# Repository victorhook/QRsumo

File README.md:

# QRsumo

QRsumo is a really cool sumorobot :)

Look out for more!

## Installation instructions
```
git clone https://github.com/victorhook/QRsumo.git
git submodule init && cd kicad-libraries && git submodule update --recursive
```

## Schematic

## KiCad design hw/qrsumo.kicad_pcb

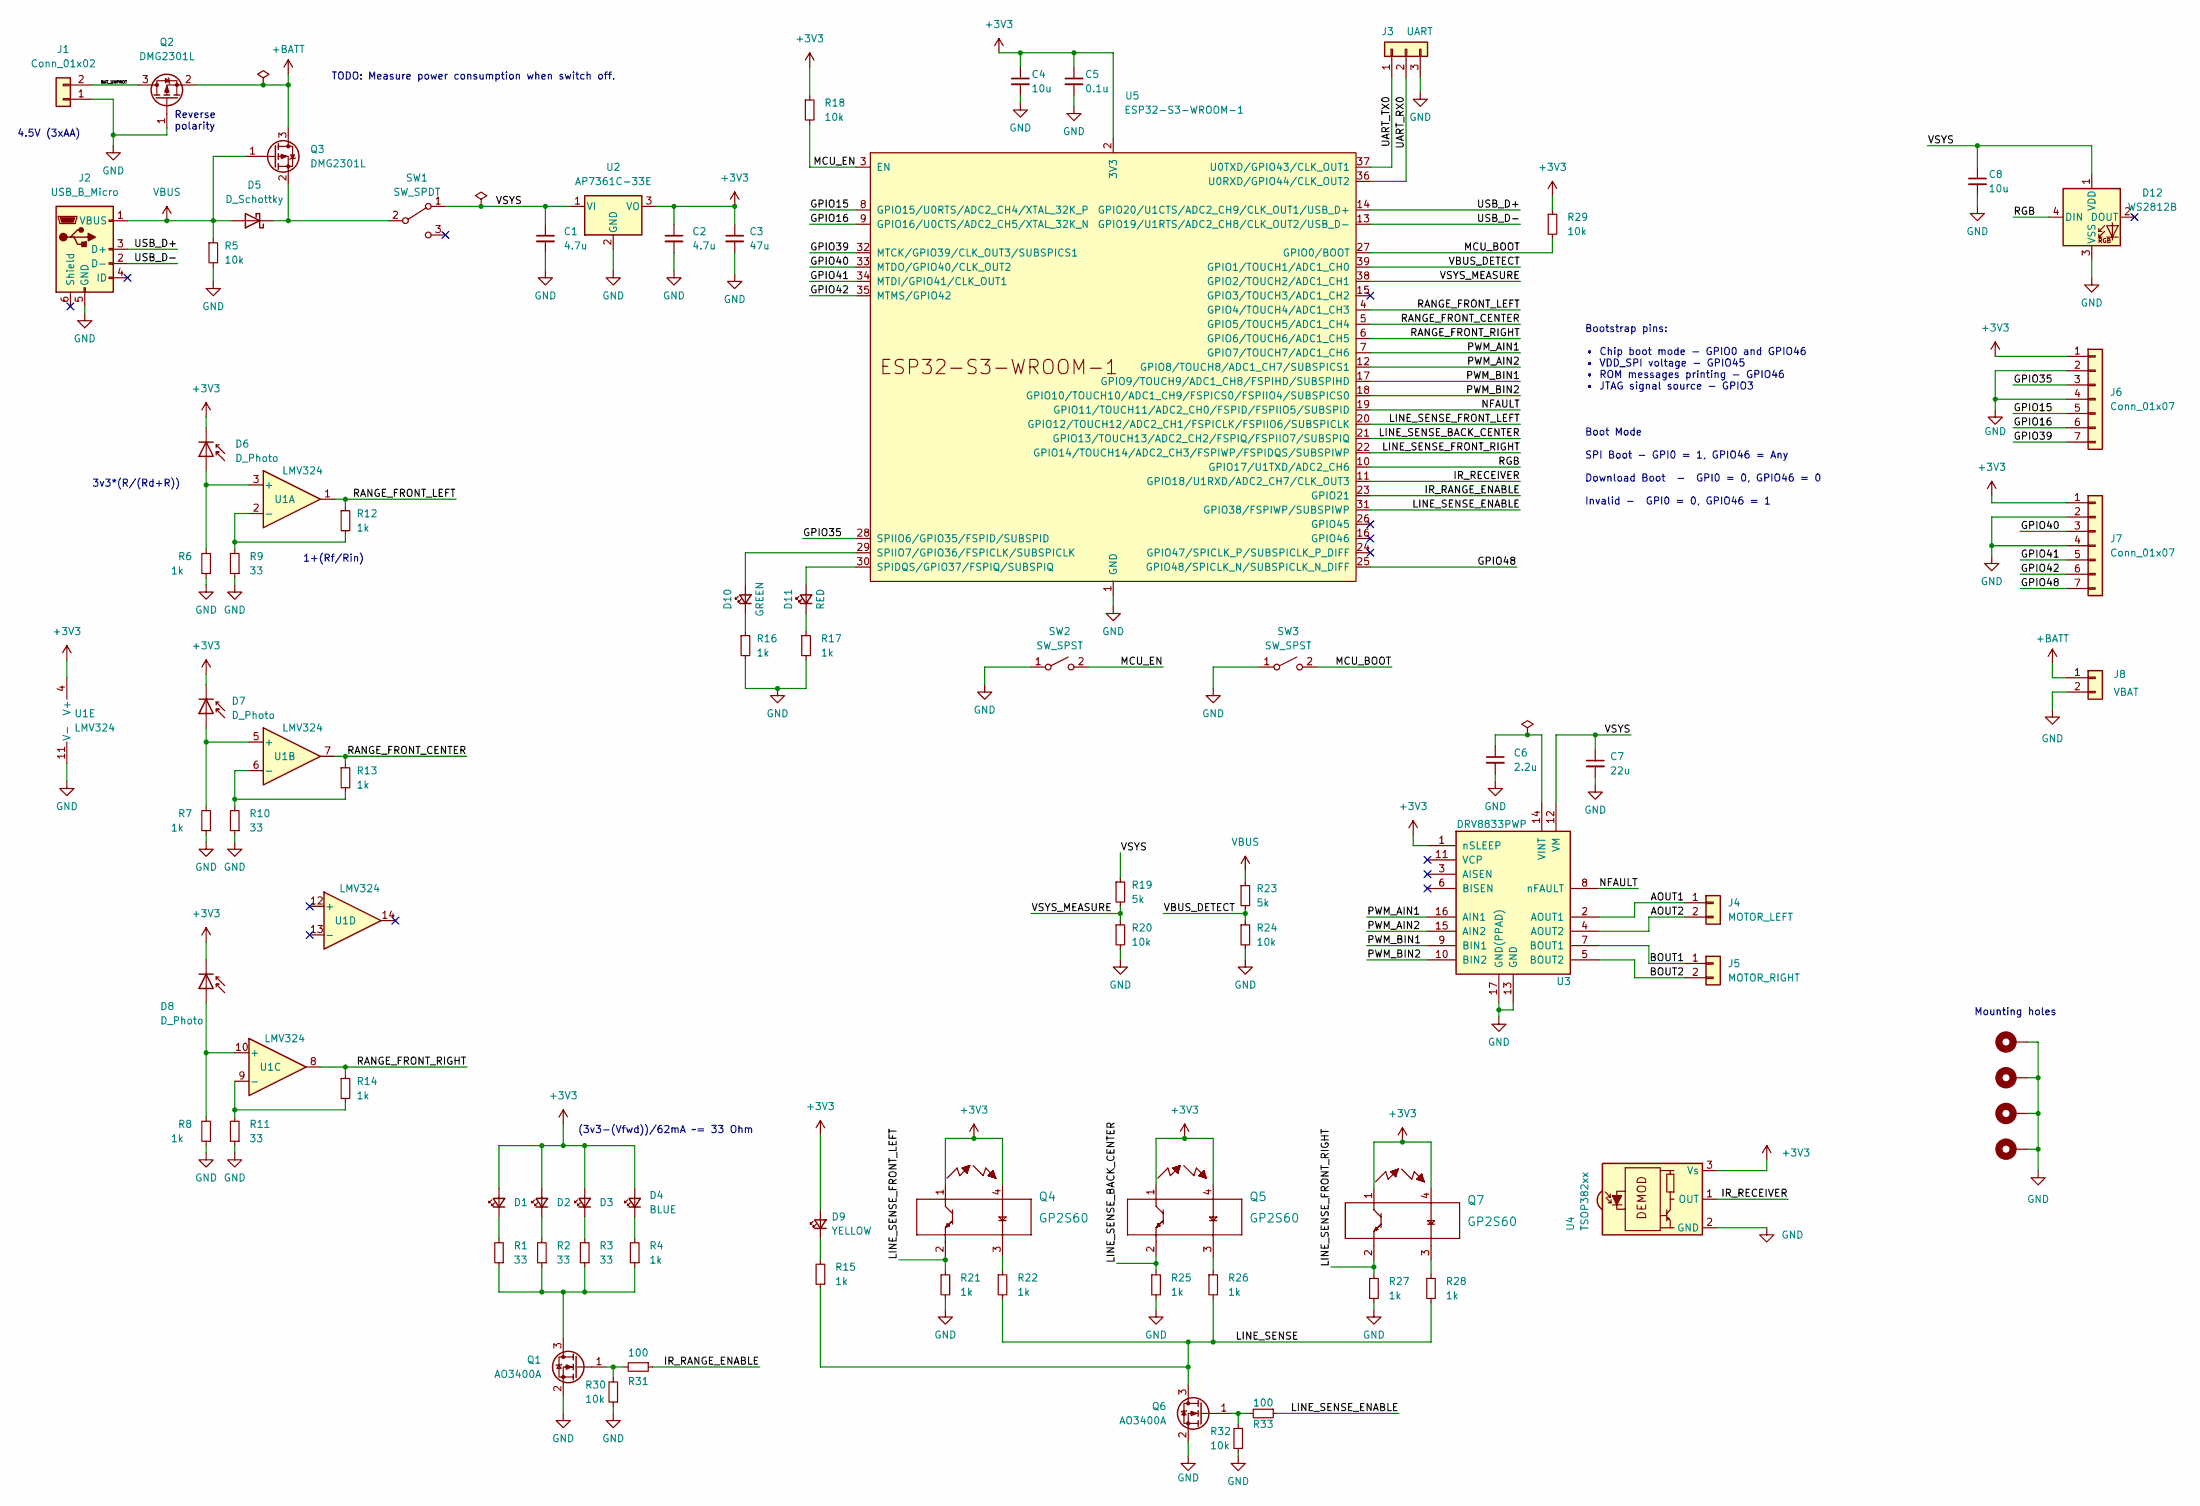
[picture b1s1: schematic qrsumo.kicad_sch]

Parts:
C1, C2: 4.7u; C_0603_1608Metric
C3: 47u; C_0603_1608Metric
C4, C8: 10u; C_0603_1608Metric
C5: 0.1u; C_0603_1608Metric
C6: 2.2u; C_0603_1608Metric
C7: 22u; C_0603_1608Metric
D1, D2, D3: LED_Small; PinHeader_1x02_P2.54mm_Vertical
D4: BLUE; LED_0603_1608Metric
D5: D_Schottky; D_SOD-123F
D6, D7, D8: D_Photo; PinHeader_1x02_P2.54mm_Vertical
D9: YELLOW; LED_0603_1608Metric
D10: GREEN; LED_0603_1608Metric
D11: RED; LED_0603_1608Metric
D12: WS2812B; LED_WS2812B_PLCC4_5.0x5.0mm_P3.2mm
H1, H2, H3, H4: MountingHole_Pad; MountingHole_2.7mm_M2.5_Pad_Via
J1: Conn_01x02; PinHeader_1x02_P2.54mm_Vertical
J2: USB_B_Micro; CONN_10118193-0001LF_AMP
J3: UART; PinHeader_1x03_P2.54mm_Vertical
J4: MOTOR_LEFT; PinHeader_1x02_P2.54mm_Vertical
J5: MOTOR_RIGHT; PinHeader_1x02_P2.54mm_Vertical
J6, J7: Conn_01x07; PinHeader_1x07_P2.54mm_Vertical
J8: VBAT; PinHeader_1x02_P2.54mm_Vertical
Q1, Q6: AO3400A; SOT-23
Q2, Q3: DMG2301L; SOT-23
Q4, Q5, Q7: GP2S60; SHARP_GP2S60
R1, R2, R3, R9, R10, R11: 33; R_0603_1608Metric
R4, R6, R7, R8, R12, R13, R14, R15, R16, R17, R21, R22, R25, R26, R27, R28: 1k; R_0603_1608Metric
R5, R18, R20, R24, R29, R30, R32: 10k; R_0603_1608Metric
R19, R23: 5k; R_0603_1608Metric
R31, R33: 100; R_0603_1608Metric
SW1: SW_SPDT; EG1206A_EWI
SW2, SW3: SW_SPST; PTS647_SPST_SNXX_SMTR2_4.5x4.5mm
U1: LMV324; TSSOP-14_4.4x5mm_P0.65mm
U2: AP7361C-33E; SOT-223-3_TabPin2; MPN AP7361C-33ER-13DITR-ND
U3: DRV8833PWP; HTSSOP-16-1EP_4.4x5mm_P0.65mm_EP3.4x5mm_Mask2.46x2.31mm_The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
U4: TSOP382xx; Vishay_MINICAST-3Pin
U5: ESP32-S3-WROOM-1; ESP32-S3-WROOM-1U

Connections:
+3V3: C2.1, C3.1, C4.1, C5.1, D1.2 (A), D2.2 (A), D3.2 (A), D4.2 (A), D6.1 (K), D7.1 (K), D8.1 (K), D9.2 (A), J6.1, J7.1, Q4.1, Q4.4, Q5.1, Q5.4, Q7.1, Q7.4, R18.1, R29.1, U1.4 (V+), U2.3 (VO), U3.1 (nSLEEP), U4.3 (Vs), U5.2 (3V3)
+BATT: J8.1, Q2.2 (S), Q3.3 (D)
/AOUT1: J4.1, U3.2 (AOUT1)
/AOUT2: J4.2, U3.4 (AOUT2)
/BAT_UNPROT: J1.2, Q2.3 (D)
/BOUT1: J5.1, U3.7 (BOUT1)
/BOUT2: J5.2, U3.5 (BOUT2)
/GPIO15: J6.5, U5.8 (GPIO15/U0RTS/ADC2_CH4/XTAL_32K_P)
/GPIO16: J6.6, U5.9 (GPIO16/U0CTS/ADC2_CH5/XTAL_32K_N)
/GPIO35: J6.3, U5.28 (SPIIO6/GPIO35/FSPID/SUBSPID)
/GPIO39: J6.7, U5.32 (MTCK/GPIO39/CLK_OUT3/SUBSPICS1)
/GPIO40: J7.3, U5.33 (MTDO/GPIO40/CLK_OUT2)
/GPIO41: J7.5, U5.34 (MTDI/GPIO41/CLK_OUT1)
/GPIO42: J7.6, U5.35 (MTMS/GPIO42)
/GPIO48: J7.7, U5.25 (GPIO48/SPICLK_N/SUBSPICLK_N_DIFF)
/IR_RANGE_ENABLE: R31.1, U5.23 (GPIO21)
/IR_RECEIVER: U4.1 (OUT), U5.11 (GPIO18/U1RXD/ADC2_CH7/CLK_OUT3)
/LINE_SENSE: Q6.3 (D), R15.1, R22.2, R26.2, R28.2
/LINE_SENSE_BACK_CENTER: Q5.2, R25.1, U5.21 (GPIO13/TOUCH13/ADC2_CH2/FSPIQ/FSPIIO7/S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)
/LINE_SENSE_ENABLE: R33.1, U5.31 (GPIO38/FSPIWP/SUBSPIWP)
/LINE_SENSE_FRONT_LEFT: Q4.2, R21.1, U5.20 (GPIO12/TOUCH12/ADC2_CH1/FSPICLK/FSPIIO6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)
/LINE_SENSE_FRONT_RIGHT: Q7.2, R27.1, U5.22 (GPIO14/TOUCH14/ADC2_CH3/FSPIWP/FSPIDQS/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)
/MCU_BOOT: R29.2, SW3.2 (B), U5.27 (GPIO0/BOOT)
/MCU_EN: R18.2, SW2.2 (B), U5.3 (EN)
/NFAULT: U3.8 (nFAULT), U5.19 (GPIO11/TOUCH11/ADC2_CH0/FSPID/FSPIIO5/S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)
/PWM_AIN1: U3.16 (AIN1), U5.7 (GPIO7/TOUCH7/ADC1_CH6)
/PWM_AIN2: U3.15 (AIN2), U5.12 (GPIO8/TOUCH8/ADC1_CH7/SUBSPICS1)
/PWM_BIN1: U3.9 (BIN1), U5.17 (GPIO9/TOUCH9/ADC1_CH8/FSPIHD/SUBSPIHD)
/PWM_BIN2: U3.10 (BIN2), U5.18 (GPIO10/TOUCH10/ADC1_CH9/FSPICS0/FSPIIO4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)
/RANGE_FRONT_CENTER: R13.1, U1.7, U5.5 (GPIO5/TOUCH5/ADC1_CH4)
/RANGE_FRONT_LEFT: R12.1, U1.1, U5.4 (GPIO4/TOUCH4/ADC1_CH3)
/RANGE_FRONT_RIGHT: R14.1, U1.8, U5.6 (GPIO6/TOUCH6/ADC1_CH5)
/RGB: D12.4 (DIN), U5.10 (GPIO17/U1TXD/ADC2_CH6)
/UART_RX0: J3.2, U5.36 (U0RXD/GPIO44/CLK_OUT2)
/UART_TX0: J3.1, U5.37 (U0TXD/GPIO43/CLK_OUT1)
/USB_D+: J2.3 (D+), U5.14 (GPIO20/U1CTS/ADC2_CH9/CLK_OUT1/USB_D+)
/USB_D-: J2.2 (D-), U5.13 (GPIO19/U1RTS/ADC2_CH8/CLK_OUT2/USB_D-)
/VBUS_DETECT: R23.2, R24.1, U5.39 (GPIO1/TOUCH1/ADC1_CH0)
/VSYS: C1.1, C7.1, C8.1, D12.1 (VDD), R19.1, SW1.1 (A), U2.1 (VI), U3.12 (VM)
/VSYS_MEASURE: R19.2, R20.1, U5.38 (GPIO2/TOUCH2/ADC1_CH1)
GND: C1.2, C2.2, C3.2, C4.2, C5.2, C6.2, C7.2, C8.2, D12.3 (VSS), H1.1, H2.1, H3.1, H4.1, J1.1, J2.5 (GND), J3.3, J6.2, J6.4, J7.2, J7.4, J8.2, Q1.2 (S), Q2.1 (G), Q6.2 (S), R5.2, R6.1, R7.1, R8.1, R9.1, R10.1, R11.1, R16.2, R17.2, R20.2, R21.2, R24.2, R25.2, R27.2, R30.1, R32.1, SW2.1 (A), SW3.1 (A), U1.11 (V-), U2.2 (GND), U3.13 (GND), U3.17 (GND(PPAD)), U4.2 (GND), U5.1 (GND), U5.40 (GND), U5.41 (GND)
unnamed: C6.1, U3.14 (VINT)
unnamed: D1.1 (K), R1.2
unnamed: D2.1 (K), R2.2
unnamed: D3.1 (K), R3.2
unnamed: D4.1 (K), R4.2
unnamed: D5.1 (K), Q3.2 (S), SW1.2 (B)
unnamed: D6.2 (A), R6.2, U1.3 (+)
unnamed: D7.2 (A), R7.2, U1.5 (+)
unnamed: D8.2 (A), R8.2, U1.10 (+)
unnamed: D9.1 (K), R15.2
unnamed: D10.1 (K), R16.1
unnamed: D10.2 (A), U5.29 (SPIIO7/GPIO36/FSPICLK/SUBSPICLK)
unnamed: D11.1 (K), R17.1
unnamed: D11.2 (A), U5.30 (SPIDQS/GPIO37/FSPIQ/SUBSPIQ)
unnamed: Q1.1 (G), R30.2, R31.2
unnamed: Q1.3 (D), R1.1, R2.1, R3.1, R4.1
unnamed: Q4.3, R22.1
unnamed: Q5.3, R26.1
unnamed: Q6.1 (G), R32.2, R33.2
unnamed: Q7.3, R28.1
unnamed: R10.2, R13.2, U1.6 (-)
unnamed: R11.2, R14.2, U1.9 (-)
unnamed: R9.2, R12.2, U1.2 (-)
VBUS: D5.2 (A), J2.1 (VBUS), Q3.1 (G), R5.1, R23.1

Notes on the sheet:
3v3*(R/(Rd+R))
Mounting holes
Bootstrap pins: • Chip boot mode - GPIO0 and GPIO46 • VDD_SPI voltage - GPIO45 • ROM messages printing - GPIO46 • JTAG signal source - GPIO3 Boot Mode SPI Boot - GPI0 = 1, GPIO46 = Any Download Boot - GPI0 = 0, GPIO46 = 0 Invalid - GPI0 = 0, GPIO46 = 1
Reverse polarity
TODO: Measure power consumption when switch off.
1+(Rf/Rin)
4.5V (3xAA)
(3v3-(Vfwd))/62mA ~= 33 Ohm

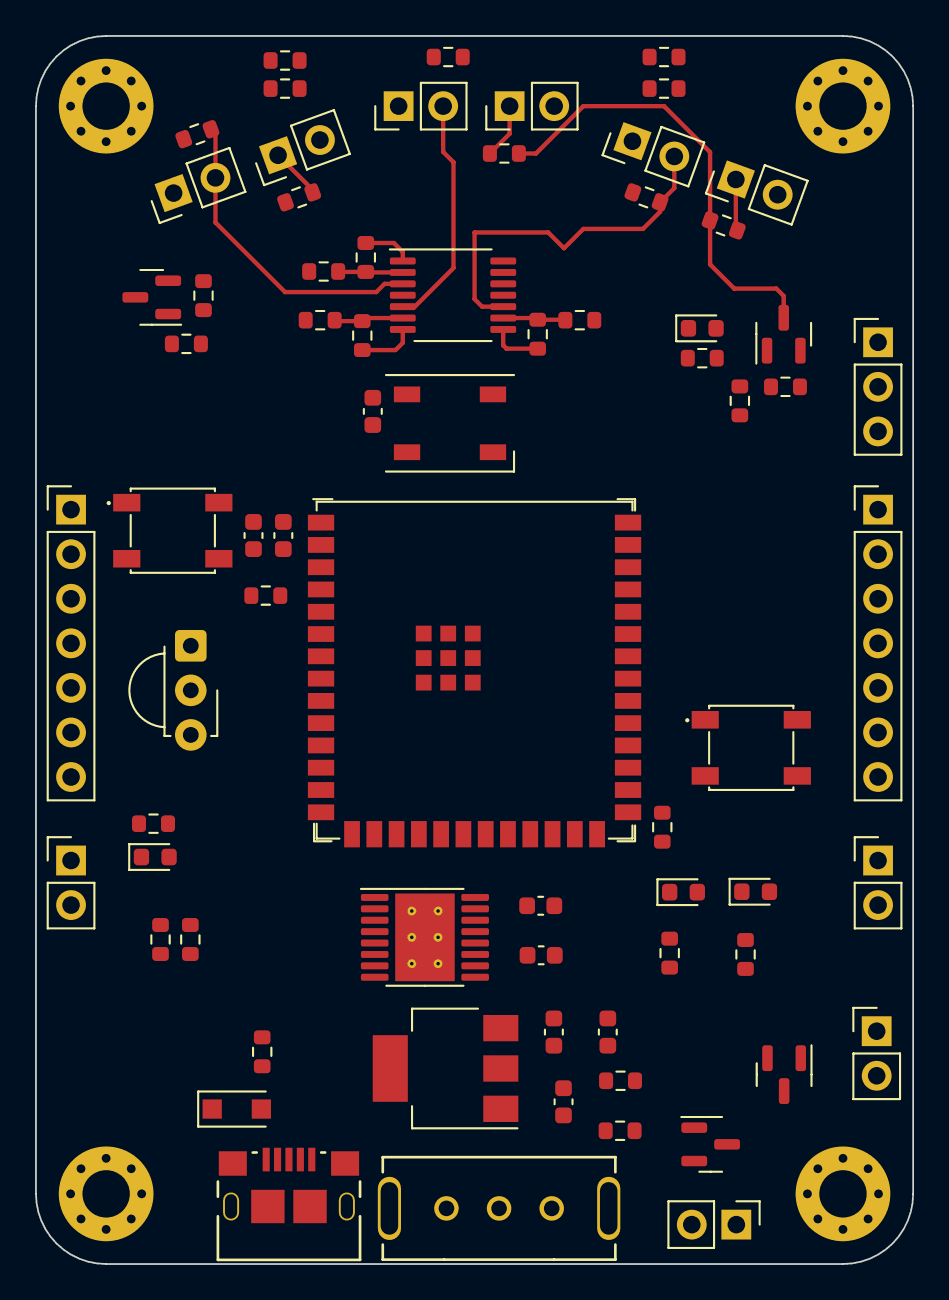
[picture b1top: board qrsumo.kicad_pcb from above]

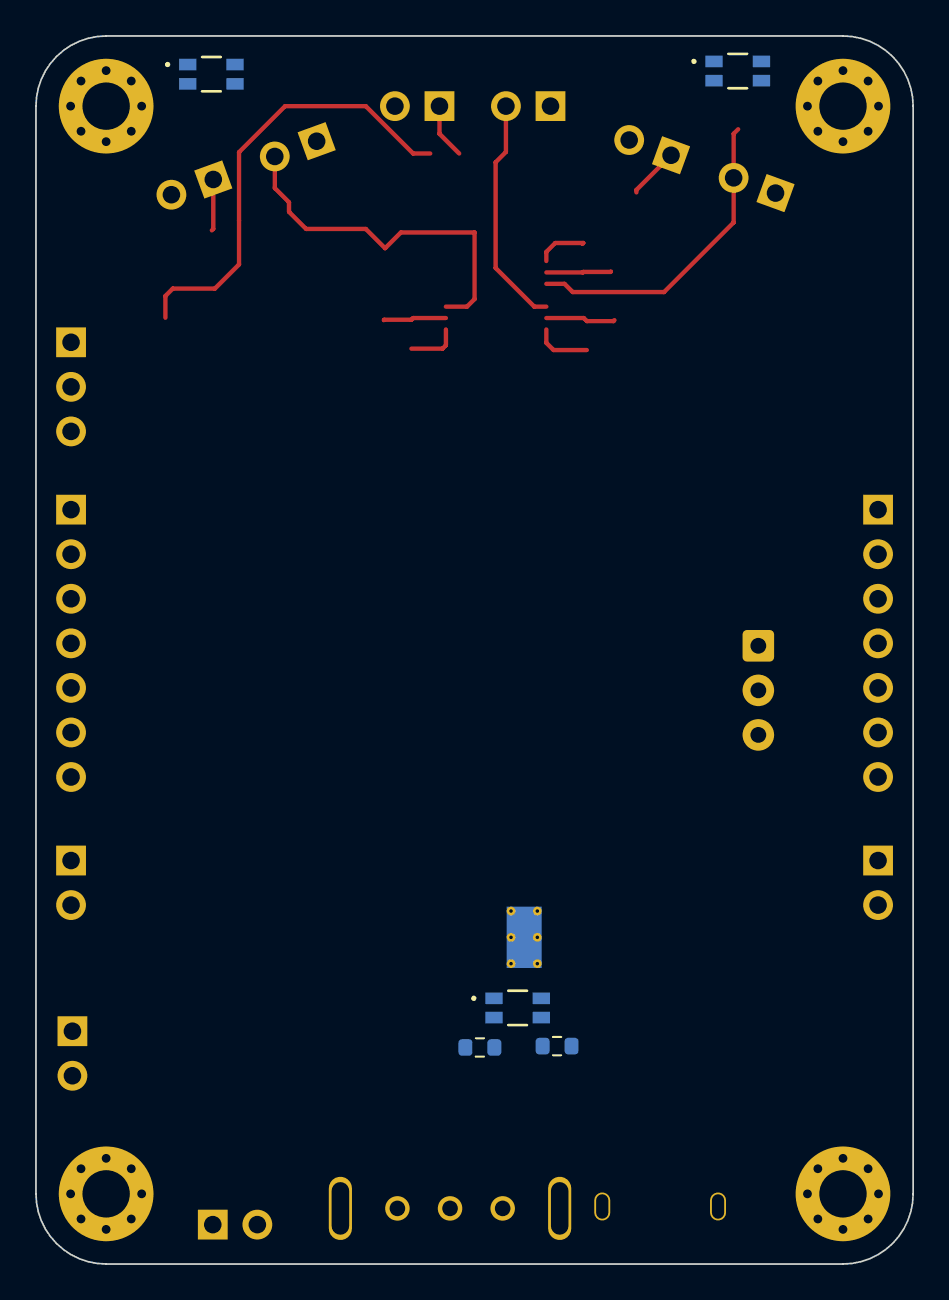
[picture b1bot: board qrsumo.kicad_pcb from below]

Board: 4 copper layers, 50.0 x 70.0 mm, 80 parts (5 on the bottom side), 65 nets.

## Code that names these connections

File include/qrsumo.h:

#ifndef QRSUMO_H
#define QRSUMO_H

#include <Arduino.h>
#include <Adafruit_NeoPixel.h>

#define PIN_VBUS_DETECT 0
#define PIN_VSYS_MEASURE 0
#define PIN_RANGE_FRONT_LEFT 0
#define PIN_RANGE_FRONT_CENTER 0
#define PIN_RANGE_FRONT_RIGHT 0
#define PIN_PWM_AIN1 0
#define PIN_PWM_AIN2 0
#define PIN_PWM_BIN1 0
#define PIN_PWM_BIN2 0
#define PIN_NFAULT 0
#define PIN_LINE_SENSE_ENABLE 0
#define PIN_LINE_SENSE_FRONT_LEFT 0
#define PIN_LINE_SENSE_BACK_CENTER 0
#define PIN_LINE_SENSE_FRONT_RIGHT 0
#define PIN_RGB 0
#define PIN_LED_GREEN 0
#define PIN_LED_RED 0
#define PIN_IR_RECEIVER 0
#define PIN_IR_RANGE_ENABLE 0


typedef enum
{
    MOTOR_LEFT  = 0,
    MOTOR_RIGHT = 1
} motor_type_t;

typedef enum
{
    DIRECTION_FORWARD  = 0,
    DIRECTION_BACKWARD = 1
} direction_t;

struct Motor {
    motor_type_t type;
    direction_t  direction;
    uint8_t      duty;
    uint8_t      pin_in1;
    uint8_t      pin_in2;
};


class QRsumo
{
    public:
        QRsumo();
        ~QRsumo();
        void init();

        /*
        Parameters:
            color: 24 bit RGB, MSB.
        */
        void ledSetRgb(const uint32_t color);
        void ledSetGreen(const bool on);
        void ledSetRed(const bool on);

        /*
        Parameters:
            motor: Which motor to set direction for.
            direction: Which direction to set.
        
        Returns true if direction was successfully set.
        */
        bool setMotorDirection(const motor_type_t motor, const direction_t direction);

        /*
        Parameters:
            motor: Which motor to set duty cycle for.
            duty: Motor duty cycle, value between 0-100.
        
        Returns true if duty cycle was successfully set.
        */
        bool setMotorDutyCycle(const motor_type_t motor, const uint8_t duty);

        /*
            Returns the battery voltages, in volts.
        */
        float getBatteryVoltage();

        /*
            Returns true if USB power is detected.
        */
        bool usbIsConnected();

        /*
            Enables or disables the line sensing sensors.
        */
        void lineSenseEnableSet(const bool enable);

        /*
            Enables or disables the ir ranging sensors.
        */
        void irRangingEnableSet(const bool enable);

    private:
        Adafruit_NeoPixel m_rgb;
        struct Motor m_motor_left;
        struct Motor m_motor_right;
        
        void blinkBootupSequence();
        void updateMotors();
        void setMotor(const Motor& motor);
};


extern QRsumo qrsumo;


#endif /* QRSUMO_H */

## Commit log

2023-05-24 Add kicad-library for esp modules as submodule
2023-05-24 Use kicad 6 branch in esp library
2023-05-24 Initial schematic draft
2023-05-30 Schematic before cleanup and footprints
2023-06-07 Schematic finished
2023-06-07 Rename project
2023-06-07 Add schematic details
2023-06-07 Remove sumobot folder
2023-06-07 - Added readme - Set up platformio project - Created initial header file for QRsumo :) - Added BOM from digikey
2023-06-07 Added submodule setup info in readme
2023-06-07 Added graphic schematic
2023-06-07 Board outline
2023-06-15 adding first layout
2023-06-21 Extended qrsumo API: - Added motor direction/duty cycle setters - Added USB sense getter - Added ir ranging/line sense sensor enable setters - Added RBG and LED setters
2023-06-21 Improve placement, fix footprints
